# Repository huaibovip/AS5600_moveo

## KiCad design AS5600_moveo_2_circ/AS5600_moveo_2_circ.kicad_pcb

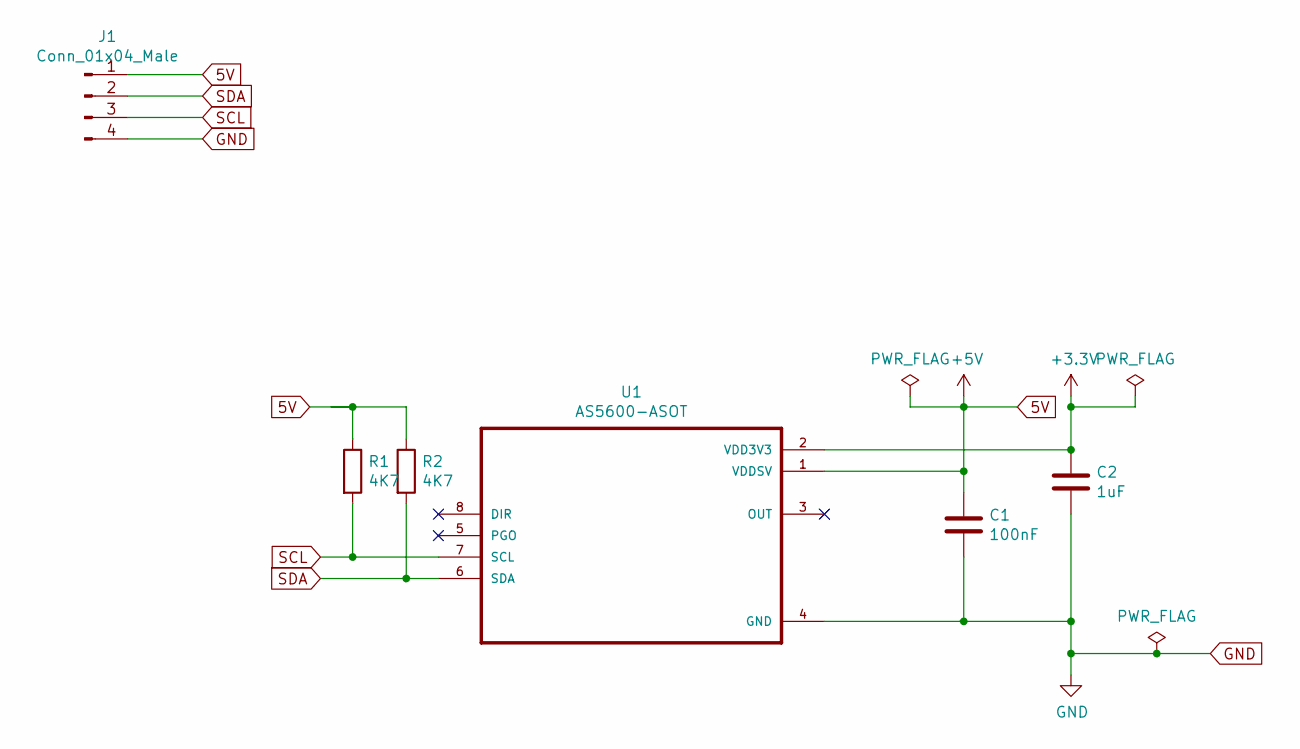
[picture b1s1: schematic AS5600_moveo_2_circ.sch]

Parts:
C1: 100nF; C_1206_3216Metric_Pad1.42x1.75mm_HandSolder
C2: 1uF; C_1206_3216Metric_Pad1.42x1.75mm_HandSolder
J1: Conn_01x04_Male; PinHeader_1x04_P2.54mm_Vertical
R1, R2: 4K7; R_1206_3216Metric_Pad1.42x1.75mm_HandSolder
U1: AS5600-ASOT; SOIC-8_3.9x4.9mm_P1.27mm

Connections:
5V: C1.1, J1.1, R1.1, R2.1, U1.1 (VDDSV)
+3V3: C2.1, U1.2 (VDD3V3)
GND: C1.2, C2.2, J1.4, U1.4 (GND)
SCL: J1.3, R1.2, U1.7 (SCL)
SDA: J1.2, R2.2, U1.6 (SDA)

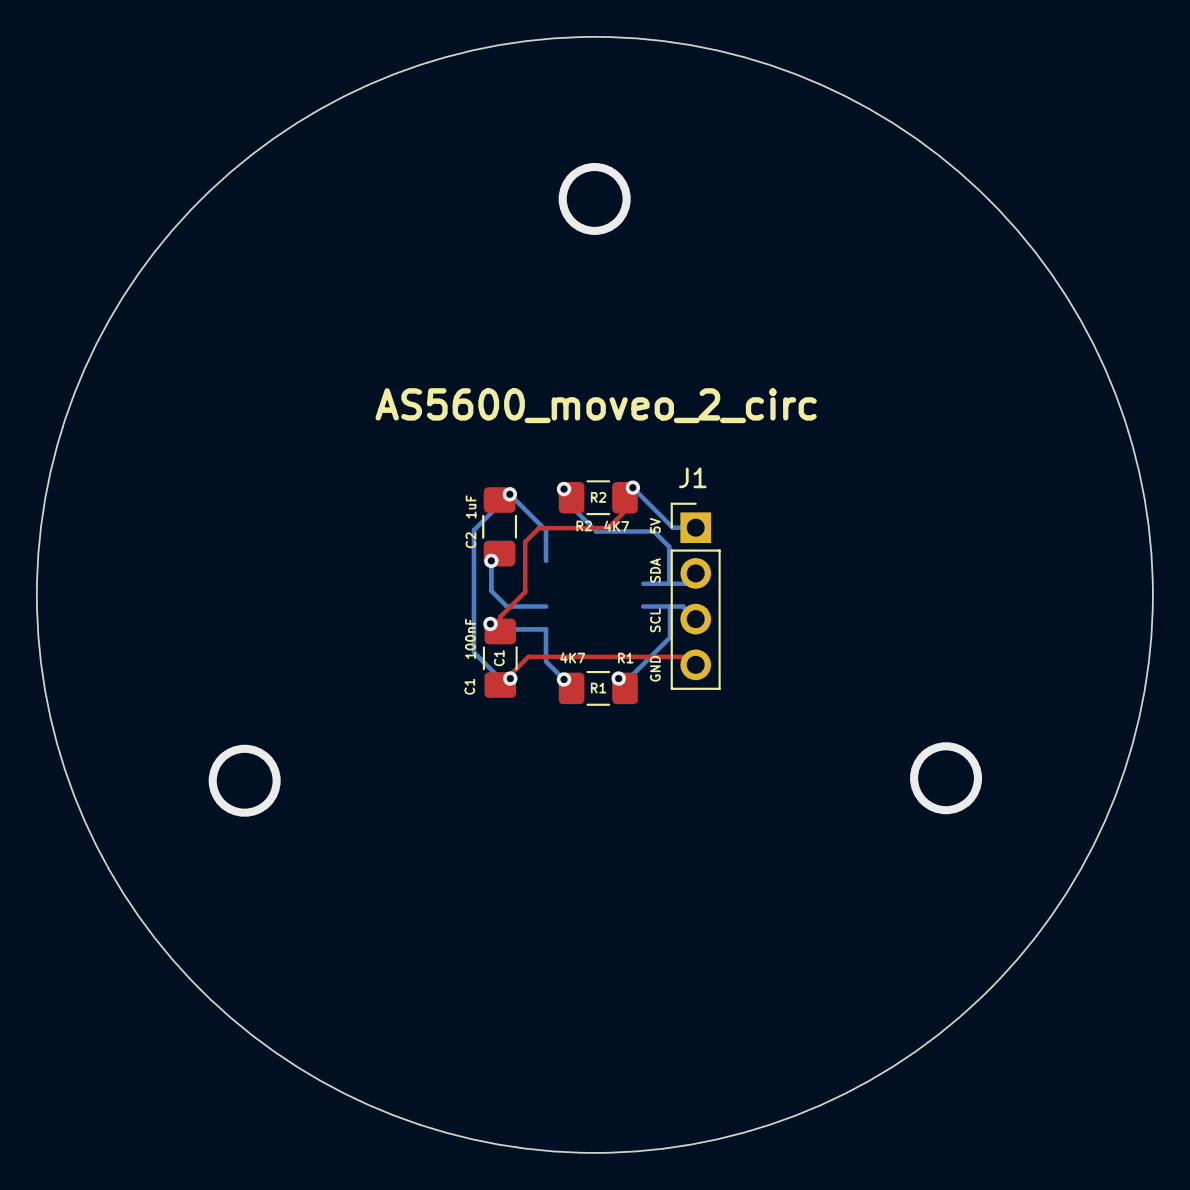
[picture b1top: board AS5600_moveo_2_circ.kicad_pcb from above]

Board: 2 copper layers, 62.0 x 62.0 mm, 6 parts (1 on the bottom side), 5 nets.

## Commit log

2018-11-27 Add files via upload
    Placas con sensor encoder AS para colocar en el moveo
